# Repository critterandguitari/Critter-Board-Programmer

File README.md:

Critter-Board-Programmer
========================

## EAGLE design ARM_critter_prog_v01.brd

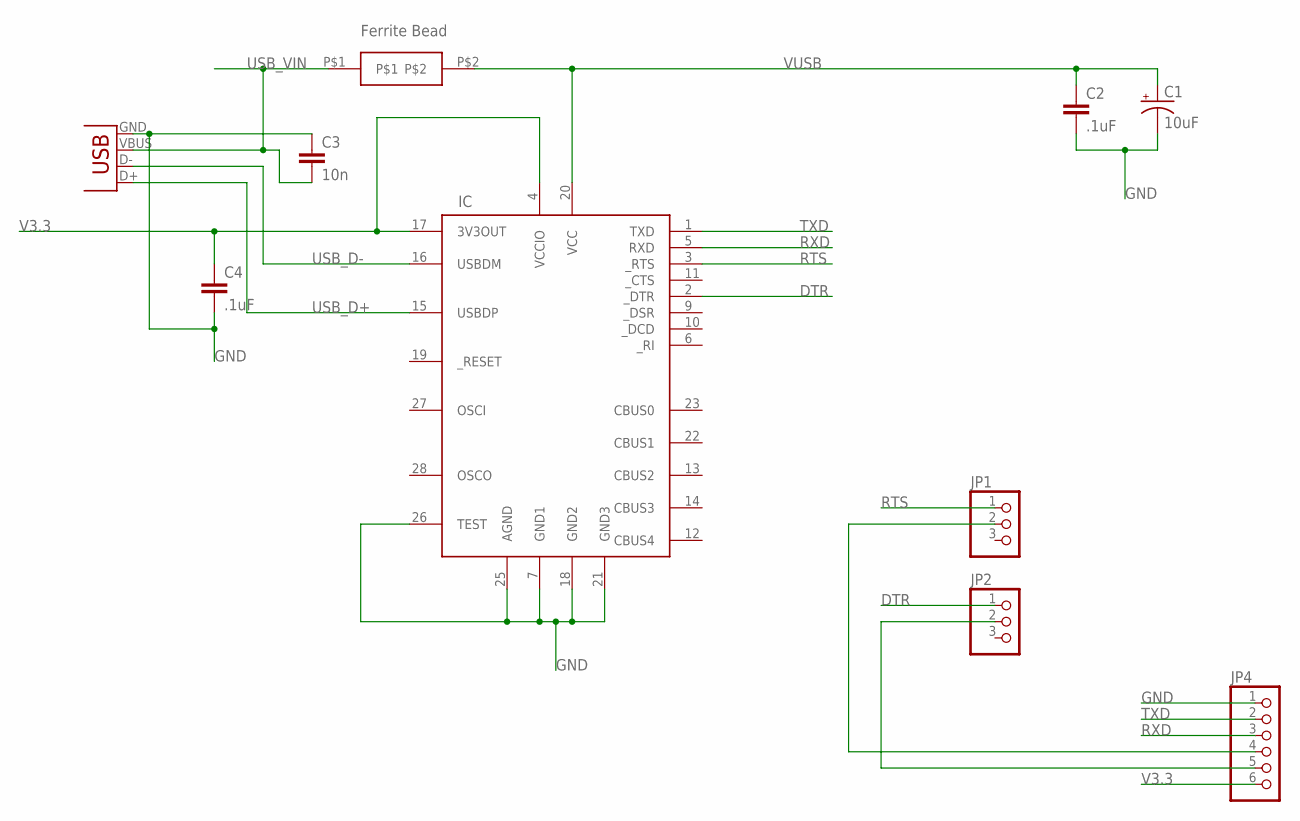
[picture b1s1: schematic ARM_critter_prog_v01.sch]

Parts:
C1: 10uF; CPOL_1206
C2, C4: .1uF; C0603
C3: 10n; C0603
IC: FT232RL; SSOP28DB
JP1, JP2: PINHD-1X3; 1X03
JP4: PINHD-1X6; 1X06
U$1: FERRITE_BEAD
X2: USB-B-H

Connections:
DTR: IC.2 (_DTR), JP2.1
GND: C1.C (-), C2.2, C3.1, C4.2, IC.7 (GND1), IC.18 (GND2), IC.21 (GND3), IC.25 (AGND), IC.26 (TEST), JP4.1, X2.GND
unnamed: JP1.2, JP4.4
unnamed: JP2.2, JP4.5
RTS: IC.3 (_RTS), JP1.1
RXD: IC.5 (RXD), JP4.3
TXD: IC.1 (TXD), JP4.2
USB_D+: IC.15 (USBDP), X2.D+
USB_D-: IC.16 (USBDM), X2.D-
USB_VIN: C3.2, U$1.P$1, X2.VBUS
V3.3: C4.1, IC.4 (VCCIO), IC.17 (3V3OUT), JP4.6
VUSB: C1.A (+), C2.1, IC.20 (VCC), U$1.P$2

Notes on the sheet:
Ferrite Bead

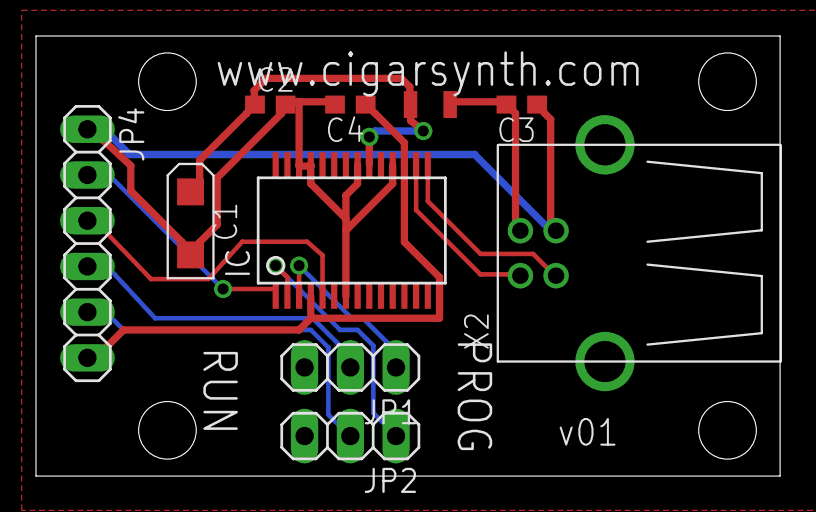
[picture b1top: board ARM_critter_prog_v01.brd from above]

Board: 2 copper layers, 41.3 x 24.4 mm, 10 parts (0 on the bottom side), 12 nets.

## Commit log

2013-04-21 adding eagle files
